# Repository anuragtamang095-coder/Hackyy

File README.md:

# Hackyy Pad

A custom 4-key macropad featuring a rotary encoder and an animated OLED display, designed and built from scratch for the Hack Club Stardance challenge.

---

## Screenshots

| Schematic | PCB Layout | 3D Case Design |
| :---: | :---: | :---: |
|  |  |  |

---

## Bill of Materials (BOM)

- **1x** Custom PCB (designed in KiCad)
- **1x** 3D Printed Enclosure (Top and Bottom halves)
- **1x** Seeed Studio XIAO RP2040 Microcontroller
- **4x** Mechanical Switches
- **4x** Keycaps
- **1x** Rotary Encoder + Knob
- **1x** 0.91" I2C OLED Display

---

## Layout & Workflow Shortcuts

I designed this pad as a dedicated desk companion to streamline deep-work sessions, audio control, and quick multitasking:

* **Rotary Encoder (Knob):** 
  * **Turn:** Smooth master volume adjustment
  * **Click:** Toggle Play / Pause media
* **Switch 1:** Quick system audio mute (lifesaver for surprise calls)
* **Switch 2:** Skip to next track
* **Switch 3:** Instant virtual desktop toggle (my dedicated "hide distractions / focus" button)
* **Switch 4:** Custom macro that automatically types out my Gumroad project link
* **OLED Display:** Runs a custom **Bongo Cat** animation that rapidly taps its paws along in real-time whenever I press a key or twist the knob!

---

## The Build Journey & What I Learned

### Hardware & Enclosure
- **KiCad PCB Design:** Routed the board around the Seeed Studio XIAO RP2040. Since it's a compact 4-key layout, I was able to skip the complexity of a traditional diode matrix and wired each switch directly from a GPIO pin to ground.
- **3D Modeling in Onshape:** Designed a custom two-part enclosure from scratch. The hardest part was dialing in the exact fit tolerances so the OLED glass, mechanical switch plate, and rotary encoder sat flush without flexing or rattling.

### Firmware & QMK
- **Directory Structure:** QMK was tough to configure at first. I learned the hard way that files can't just live anywhere—they have to follow strict nesting rules (`keyboards/hackyy_pad/keymaps/default`) for the build pipeline to compile.
- **Pin Mapping:** Translated physical schematic connections into digital pinouts inside `keyboard.json` to make sure the RP2040's GPIO lines synced up with the switch matrix.

### Pairing with AI as a Tutor
Rather than just copying and pasting blocks of code, I used AI as an interactive pair-programmer to:
- Learn core CAD constraints and modeling concepts in Onshape.
- Decode walls of cryptic red GCC compiler errors (like hunting down a rogue lowercase letter in an `enum` definition that brought down the whole build).
- Build the frame-swapping logic required to render the Bongo Cat bitmap without lagging key-input responsiveness.

---

## The 1.5-Hour Tragedy 😭

The most painful bug of this entire project had nothing to do with C code, trace routing, or 3D tolerances—it was time tracking.

I spent over an hour and a half deep in the zone writing firmware and debugging, only to discover that my **Hackatime** session had been logging to the completely wrong project on the Stardance dashboard. Over 1.5 hours of tracked work vanished into the void. But a end got the time back.

**Lesson learned:** Always double-check your active project before locking into a build sprint!

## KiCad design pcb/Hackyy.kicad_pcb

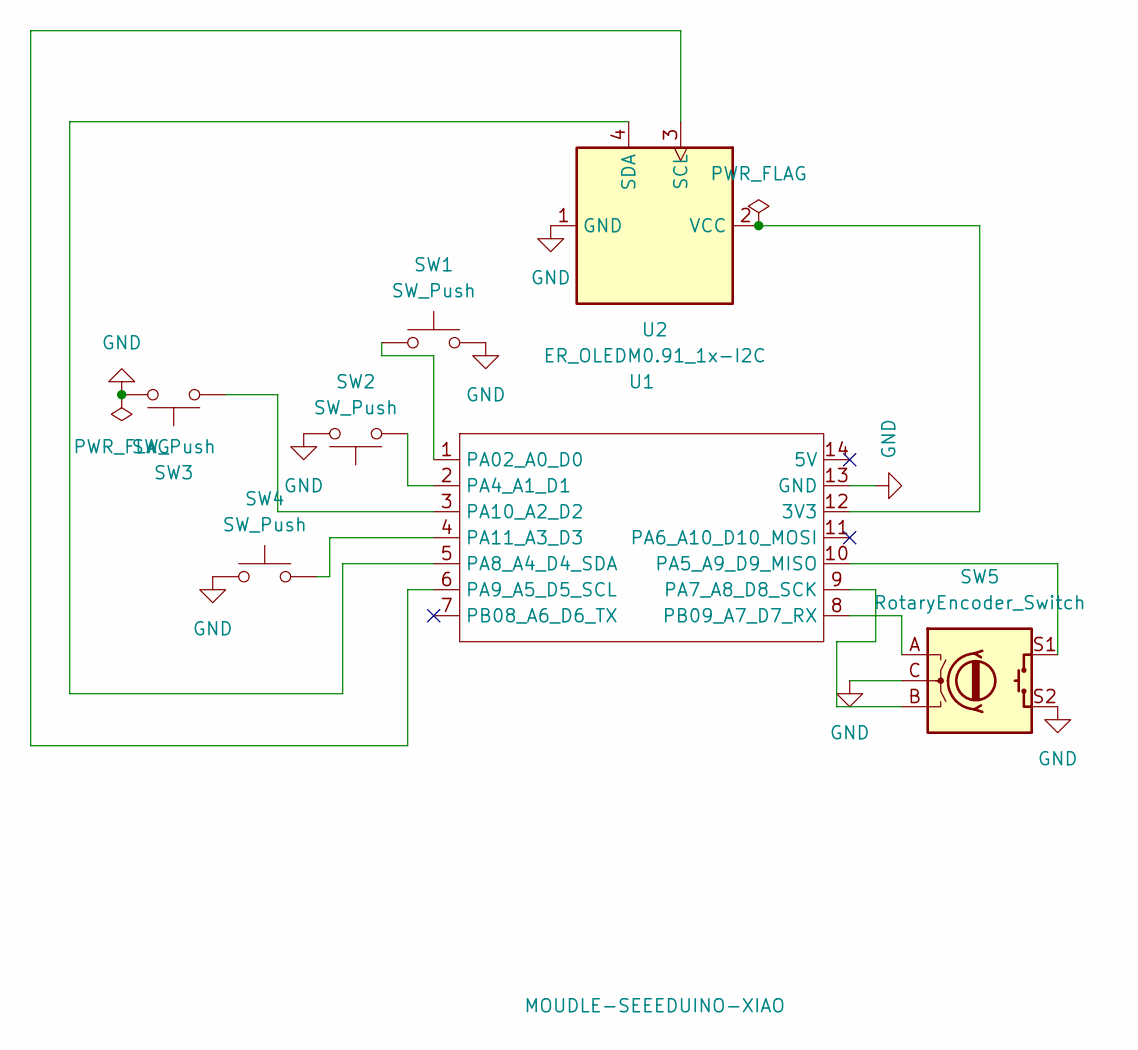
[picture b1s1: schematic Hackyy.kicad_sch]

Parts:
SW1, SW2, SW3, SW4: SW_Push; SW_Cherry_MX_1.00u_PCB
SW5: RotaryEncoder_Switch; RotaryEncoder_Alps_EC11E-Switch_Vertical_H20mm
U1: MOUDLE-SEEEDUINO-XIAO; XIAO-Generic-Hybrid-14P-2.54-21X17.8MM
U2: ER_OLEDM0.91_1x-I2C; FanPinHeader_1x04_P2.54mm_Vertical

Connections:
GND: SW1.2, SW2.2, SW3.2, SW4.1, SW5.C, SW5.S2, U1.13 (GND), U2.1 (GND)
unnamed: U1.12 (3V3), U2.2 (VCC)
unnamed: SW1.1, U1.1 (PA02_A0_D0)
unnamed: SW2.1, U1.2 (PA4_A1_D1)
unnamed: SW5.S1, U1.10 (PA5_A9_D9_MISO)
unnamed: SW5.B, U1.9 (PA7_A8_D8_SCK)
unnamed: U1.5 (PA8_A4_D4_SDA), U2.4 (SDA)
unnamed: U1.6 (PA9_A5_D5_SCL), U2.3 (SCL)
unnamed: SW3.1, U1.3 (PA10_A2_D2)
unnamed: SW4.2, U1.4 (PA11_A3_D3)
unnamed: SW5.A, U1.8 (PB09_A7_D7_RX)

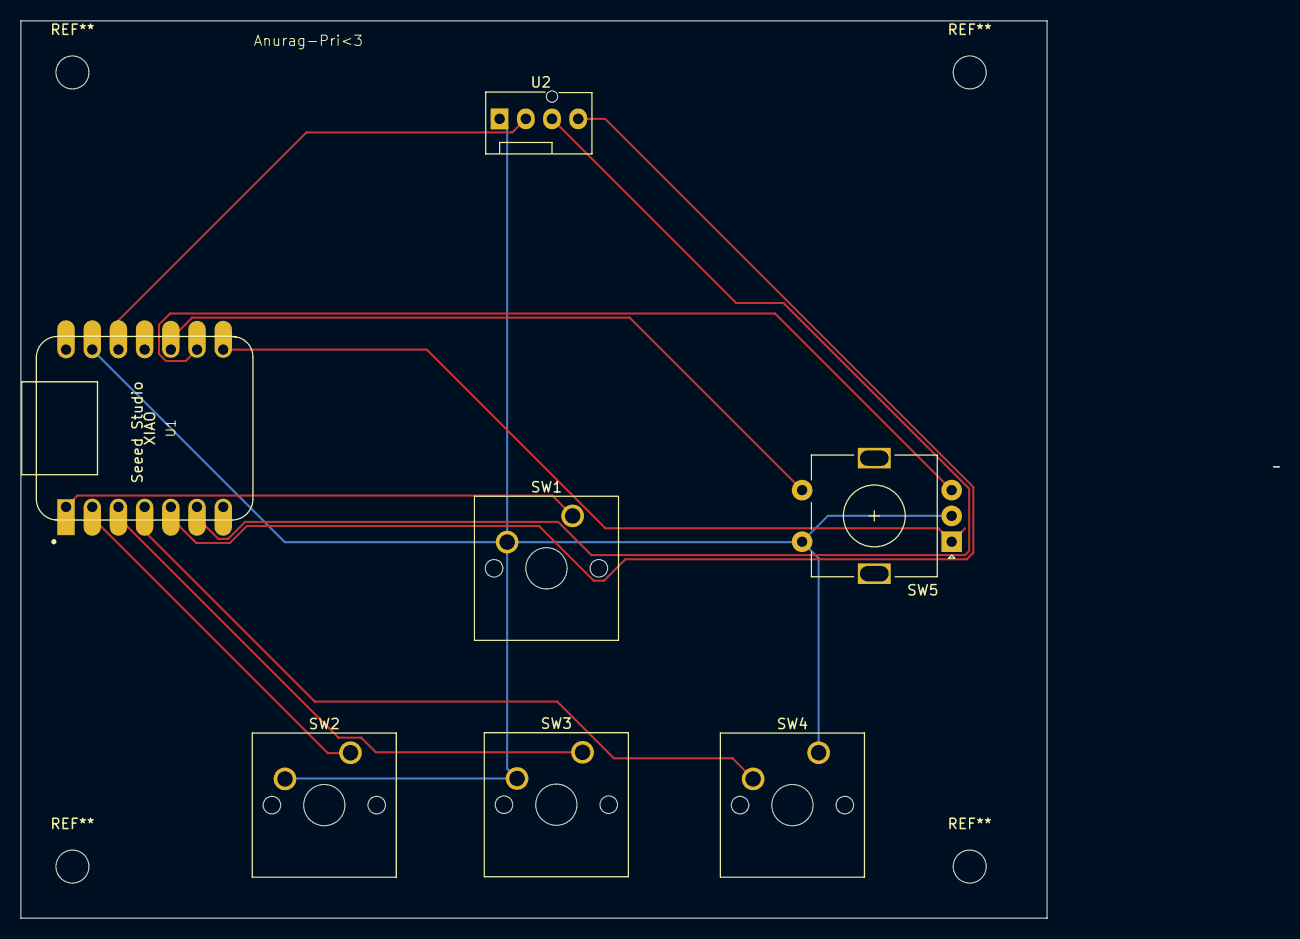
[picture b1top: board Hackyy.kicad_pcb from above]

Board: 2 copper layers, 99.5 x 87.0 mm, 7 parts (0 on the bottom side), 11 nets.
